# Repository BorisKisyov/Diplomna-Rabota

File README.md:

# Diplomna-Rabota
Дипломната работа на Борис Кисьов. Ученик в ТУЕС от 12"г" клас 2022/2023 година. 
Темата на проекта е "Система за наблюдение на горски масиви на базата на LoRa".

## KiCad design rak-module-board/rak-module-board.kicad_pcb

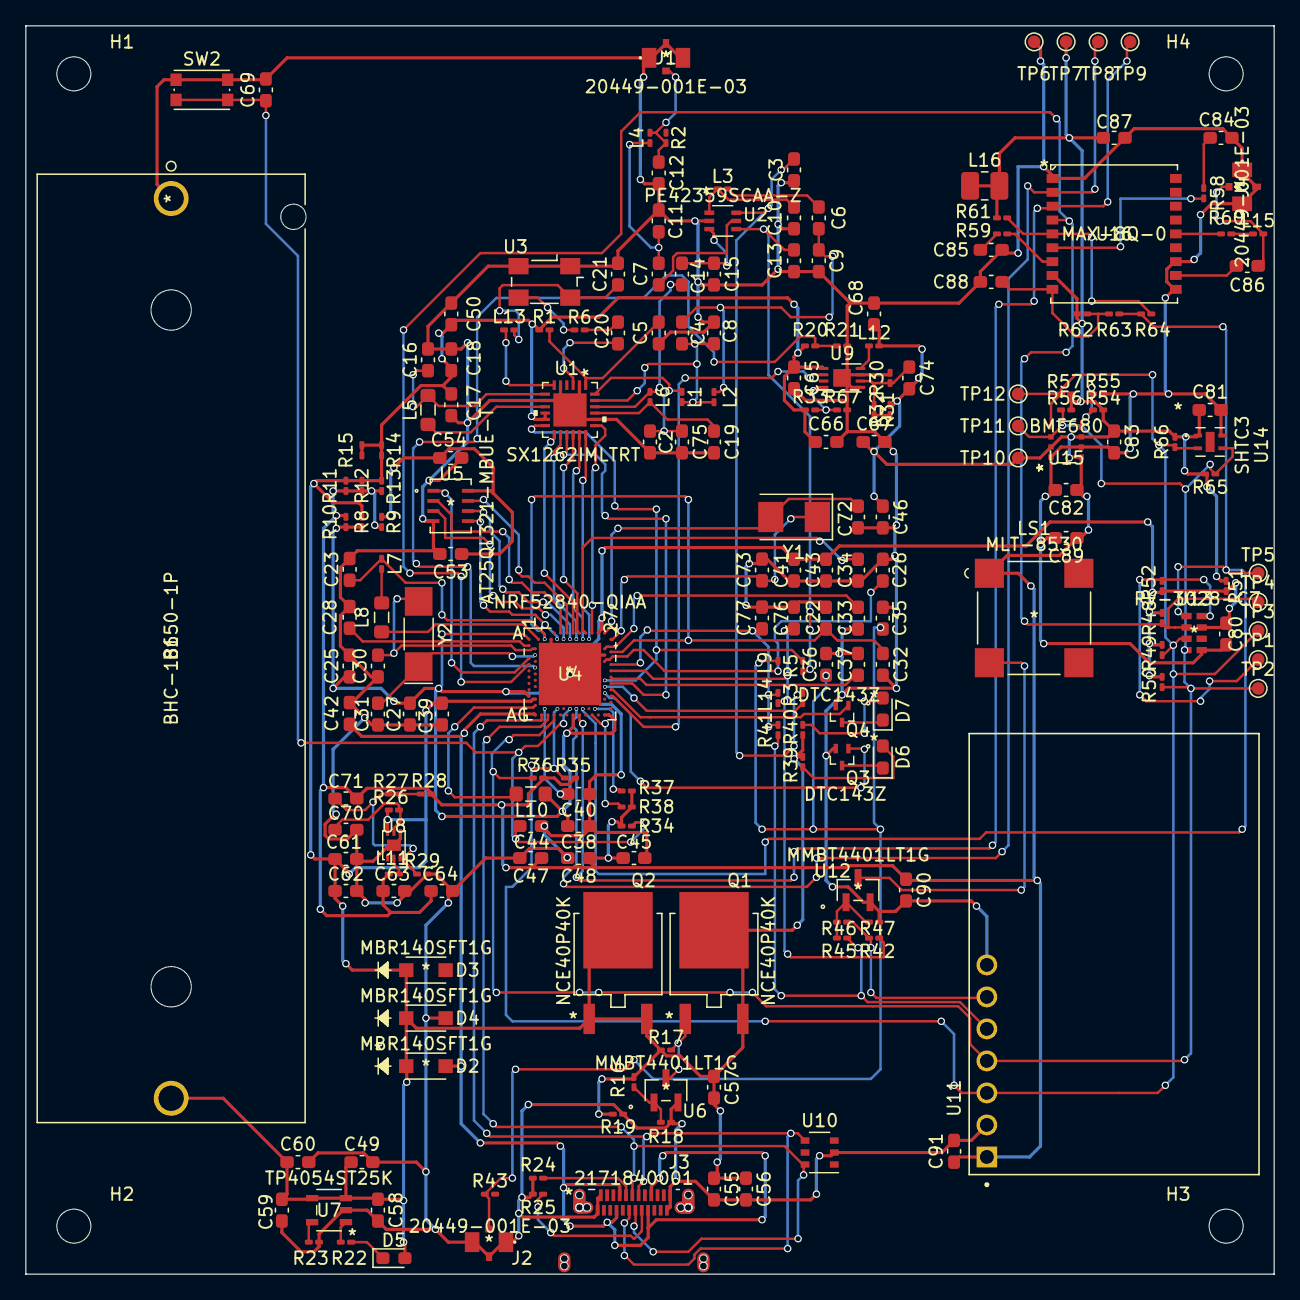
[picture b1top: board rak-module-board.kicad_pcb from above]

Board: 2 copper layers, 99.1 x 99.1 mm, 214 parts (0 on the bottom side), 109 nets.

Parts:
B1: BHC-18650-1P
C2: 47pF; C_0603_1608Metric_Pad1.08x0.95mm_HandSolder
C3, C13, C37: 1nF; C_0603_1608Metric_Pad1.08x0.95mm_HandSolder
C4, C22, C25, C58, C70, C88: 1uF; C_0603_1608Metric_Pad1.08x0.95mm_HandSolder
C5: 3pF; C_0603_1608Metric_Pad1.08x0.95mm_HandSolder
C6, C7: 39pF; C_0603_1608Metric_Pad1.08x0.95mm_HandSolder
C8, C15, C26, C32, C36, C45: NC; C_0603_1608Metric_Pad1.08x0.95mm_HandSolder
C9: 5.6pF; C_0603_1608Metric_Pad1.08x0.95mm_HandSolder
C10: 3.3pF; C_0603_1608Metric_Pad1.08x0.95mm_HandSolder
C11, C12: 3.9pF; C_0603_1608Metric_Pad1.08x0.95mm_HandSolder
C14: 2.4pF; C_0603_1608Metric_Pad1.08x0.95mm_HandSolder
C16: 470nF; C_0603_1608Metric_Pad1.08x0.95mm_HandSolder
C17, C18, C21, C27, C28, C41, C43, C44, C47, C48, C49, C50, C53, C54, C55, C56, C57, C61, C62, C63, C64, C65, C66, C67, C68, C69, C75, C80, C81, C82, C83, C85, C87, C89, C90, C91: 100nF; C_0603_1608Metric_Pad1.08x0.95mm_HandSolder
C19: 1.8pF; C_0603_1608Metric_Pad1.08x0.95mm_HandSolder
C20: 10pF; C_0603_1608Metric_Pad1.08x0.95mm_HandSolder
C23: 47nF; C_0603_1608Metric_Pad1.08x0.95mm_HandSolder
C30, C31, C71, C74: 22pF; C_0603_1608Metric_Pad1.08x0.95mm_HandSolder
C33, C86: 100pF; C_0603_1608Metric_Pad1.08x0.95mm_HandSolder
C34, C35: 1pF; C_0603_1608Metric_Pad1.08x0.95mm_HandSolder
C38, C39, C40, C42: 4.7uF; C_0603_1608Metric_Pad1.08x0.95mm_HandSolder
C46, C84: 10uF; C_0603_1608Metric_Pad1.08x0.95mm_HandSolder
C59, C60: 100uF; C_0603_1608Metric_Pad1.08x0.95mm_HandSolder
C72, C73: 12pF; C_0603_1608Metric_Pad1.08x0.95mm_HandSolder
C76, C77: 300pF; C_0603_1608Metric_Pad1.08x0.95mm_HandSolder
D2, D3, D4: MBR140SFT1G
D5: RED; LED_0603_1608Metric_Pad1.05x0.95mm_HandSolder
D6: GREEN; LED_0603_1608Metric_Pad1.05x0.95mm_HandSolder
D7: BLUE; LED_0603_1608Metric_Pad1.05x0.95mm_HandSolder
H1, H2, H3, H4: MountingHole; MountingHole_2.7mm
J1, J2, J4: 20449-001E-03
J3: 2171840001
L1, L15: 47nH; L_0201_0603Metric_Pad0.64x0.40mm_HandSolder
L2: 2.5nH; L_0201_0603Metric_Pad0.64x0.40mm_HandSolder
L3: 4.7nH; L_0201_0603Metric_Pad0.64x0.40mm_HandSolder
L4: 9.1nH; L_0201_0603Metric_Pad0.64x0.40mm_HandSolder
L5: 15uH; L_0805_2012Metric_Pad1.05x1.20mm_HandSolder
L6: 15nH; L_0201_0603Metric_Pad0.64x0.40mm_HandSolder
L7: 13nH; L_0201_0603Metric_Pad0.64x0.40mm_HandSolder
L8, L10: 10uH; L_0805_2012Metric_Pad1.05x1.20mm_HandSolder
L9: 3.9nH; L_0201_0603Metric_Pad0.64x0.40mm_HandSolder
L11: 4.7uH; L_0201_0603Metric_Pad0.64x0.40mm_HandSolder
L12: 2.2uH; L_0201_0603Metric_Pad0.64x0.40mm_HandSolder
L13: 120uH; L_0201_0603Metric_Pad0.64x0.40mm_HandSolder
L14: NC; L_0201_0603Metric_Pad0.64x0.40mm_HandSolder
L16: 120uH; L_1008_2520Metric_Pad1.43x2.20mm_HandSolder
LS1: MLT-8530
Q1, Q2: NCE40P40K
Q3, Q4: DTC143Z; DTC143ZEBTL
R1, R9, R11, R12, R14, R41, R42, R51, R55, R58, R59, R63: 0; R_0201_0603Metric_Pad0.64x0.40mm_HandSolder
R2, R8, R10, R13, R15, R43, R45, R54, R56, R57, R64, R65, R66, R67: NC; R_0201_0603Metric_Pad0.64x0.40mm_HandSolder
R3, R5: 100R; R_0201_0603Metric_Pad0.64x0.40mm_HandSolder
R6: 220; R_0201_0603Metric_Pad0.64x0.40mm_HandSolder
R16: 47K; R_0201_0603Metric_Pad0.64x0.40mm_HandSolder
R17, R19, R32: 100K; R_0201_0603Metric_Pad0.64x0.40mm_HandSolder
R18, R33, R34, R48, R49, R50, R52: 10K; R_0201_0603Metric_Pad0.64x0.40mm_HandSolder
R20, R29: 1M; R_0201_0603Metric_Pad0.64x0.40mm_HandSolder
R21, R28: 1.5M; R_0201_0603Metric_Pad0.64x0.40mm_HandSolder
R22: 1k; R_0201_0603Metric_Pad0.64x0.40mm_HandSolder
R23: 2.7k; R_0201_0603Metric_Pad0.64x0.40mm_HandSolder
R24, R25: 4.7k; R_0201_0603Metric_Pad0.64x0.40mm_HandSolder
R26: 100k; R_0201_0603Metric_Pad0.64x0.40mm_HandSolder
R27: 800k; R_0201_0603Metric_Pad0.64x0.40mm_HandSolder
R30: 32.4K; R_0201_0603Metric_Pad0.64x0.40mm_HandSolder
R31: 2K; R_0201_0603Metric_Pad0.64x0.40mm_HandSolder
R35, R36, R37, R38, R47, R61, R62: 4.7K; R_0201_0603Metric_Pad0.64x0.40mm_HandSolder
R39, R40: 1K; R_0201_0603Metric_Pad0.64x0.40mm_HandSolder
R46: 330; R_0201_0603Metric_Pad0.64x0.40mm_HandSolder
R60: 10; R_0201_0603Metric_Pad0.64x0.40mm_HandSolder
SW2: SW_DPST_x2; SW_Push_1P1T_NO_CK_KMR2
TP1, TP2, TP3, TP4, TP5, TP6, TP7, TP8, TP9, TP10, TP11, TP12: TestPoint; TestPoint_Pad_D1.0mm
U1: SX1262IMLTRT
U2: PE42359SCAA-Z
U3: 32MHz; Oscillator_SMD_Fox_FT5H_5.0x3.2mm
U4: NRF52840-QIAA; NRF52840-QIAA-R
U5: AT25QL321-MBUE-T
U6, U12: MMBT4401LT1G
U7: TP4054ST25K
U8: SGM6036-ADJ
U9: SGM6019; TDFN-8-1EP_3x2mm_P0.5mm_EP1.4x1.4mm
U10: LRC399-04AT1G; TSOP-6_1.65x3.05mm_P0.95mm
U11: SCD30; MODULE_SCD30
U13: RV-3028-C7; RV-3028-C7 32.768KHZ 1PPM-TA-QA
U14: SHTC3
U15: BME680
U16: MAX-8Q-0
Y1: 32MHz; Crystal_SMD_5032-2Pin_5.0x3.2mm
Y2: 32.768K; Crystal_SMD_MicroCrystal_CC4V-T1A-2Pin_5.0x1.9mm_HandSolder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

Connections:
+3V3: C45.1, C46.1, C47.1, C48.1, C63.1, C64.1, C67.1, C68.1, C71.2, C74.2, C81.1, C82.1, C83.1, C87.1, C89.1, C90.1, C91.1, L11.2, L12.2, L16.1, L16.2, LS1.1, R9.1, R10.1, R11.1, R12.1, R13.1, R28.2, R32.2, R34.1, R35.1, R36.1, R37.1, R38.1, R51.1, R54.1, R56.2, R57.2, R61.1, R62.1, R65.2, R66.2, TP7.1, TP10.1, U11.1 (VDD), U14.1 (VDD), U15.2 (CSB), U15.6 (VDDIO), U15.8 (VDD), U16.8 (VCC)
+BATT: B1.2, C17.1, C18.1, C39.1, C49.1, C50.1, C55.1, C56.1, C57.1, C57.2, C58.1, C59.1, C60.1, C61.1, C62.1, C65.1, C66.1, D2.1 (K), D3.1 (K), D4.1 (K), D5.2 (A), Q1.2, Q1.3, Q2.1, Q2.2, Q2.3, R1.1, R8.2, R11.2, R12.2, R13.2, R14.1, R14.2, R15.1, R15.2, R16.1, R17.2, R19.1, R20.1, R26.1, R33.1, R39.1, R40.1, U1.10 (VBAT), U1.11 (VBAT_IO), U4.Y2 (VDDH), U7.3 (BAT), U7.4 (VCC), U8.6 (VIN), U9.1 (VIN)
/32M_TCXO: C20.2, U1.3 (XTA)
/ADC_VBAT: R20.2, R21.1, U4.K2 (P0-05/AIN3)
/ANT_SW: R3.1, U4.T23 (P1-05)
/BUSY: U1.14 (BUSY), U4.B15 (P1-14)
/DEC4_6: C22.1, C23.1, C32.1, L7.1, U4.B5 (DEC4), U4.E24 (DEC6)
/DIO1: U1.13 (DIO1), U4.A14 (P1-15)
/DIO2: R5.1, U1.12 (DIO2), U4.P23 (P1-07)
/DIO3: L13.1, U1.6 (DIO3)
/I2C_SCL: R35.2, R49.2, R57.1, R66.1, TP3.1, TP12.1, U4.AC9 (P0-14), U11.3 (TX/SCL), U13.3 (SCL), U14.2 (SCL), U15.4 (SCK)
/I2C_SCL_2: R37.2, U4.AC21 (P0-25)
/I2C_SDA: R36.2, R50.2, R56.1, R65.1, TP2.1, TP11.1, U4.AD8 (P0-13), U11.4 (RX/SDA), U13.4 (SDA), U14.3 (SDA), U15.3 (SDI)
/I2C_SDA_2: R38.2, U4.AD20 (P0-24)
/IO5: R42.2, R46.1, U11.6 (PWM)
/IO6: R41.2, R45.1, U11.5 (RDY)
/LED1: Q3.1 (B), U4.V23 (P1-03)
/LED2: Q4.1 (B), U4.U24 (P1-04)
/NFC1: C76.1, L14.2, R42.1, U4.L24 (P0-09/NFC1)
/NFC2: C77.1, L14.1, R41.1, U4.J24 (P0-10/NFC2)
/NRESET: U1.15 (NRESET), U4.R24 (P1-06)
/NRF_RESET: C44.1, C69.1, R34.2, SW2.2 (B), U4.AC13 (P0-18/NRESET)
/PO-04/AIN2: R48.2, TP4.1, U4.J1 (P0-04/AIN2), U13.2 (INT), U16.4 (TIMEPULSE)
/QSPI_CLK: U4.B13 (P0-03/AIN1), U5.6
/QSPI_CS: U4.G1 (P0-26), U5.1
/QSPI_DIO0: U4.B9 (P0-30/AIN6), U5.5
/QSPI_DIO1: U4.A10 (P0-29/AIN5), U5.2
/QSPI_DIO2: U4.B11 (P0-28/AIN4), U5.3
/QSPI_DIO3: U4.A12 (P0-02/AIN0), U5.7
/RESET_GPS: C88.1, R62.2, R63.2, U16.9 (RESET_IN)
/SPI_CLK: U1.18 (SCK), U4.B19 (P1-11)
/SPI_MISO: U1.16 (MISO), U4.A16 (P1-13)
/SPI_MOSI: U1.17 (MOSI), U4.B17 (P1-12)
/SPI_NSS: U1.19 (NSS), U4.A20 (P1-10)
/STANDBY: R61.2, R64.2, U16.5 (EXTINT)
/SW2: U4.W24 (P1-02), U9.2 (EN)
/UART1_DE: R63.1, R64.1, TP5.1, U4.AC17 (P0-21), U13.1 (CLKOUT)
/UART1_RX: TP8.1, U4.AC15 (P0-19), U16.2 (TXD)
/UART1_TX: TP9.1, U4.AD16, U16.3 (RXD)
/USB N: J3.A7 (DN1), J3.B7 (DN2), U4.AD4 (D-), U10.4 (I/O4)
/USB P: J3.A6 (DP1), J3.B6 (DP2), U4.AD6 (D+), U10.6 (I/O3)
GND: B1.1, C2.2, C3.1, C4.2, C8.2, C9.2, C10.2, C11.2, C12.2, C13.2, C15.2, C16.2, C17.2, C18.2, C19.2, C21.2, C22.2, C23.2, C25.2, C26.2, C27.2, C28.1, C30.1, C31.1, C32.2, C33.2, C34.2, C35.2, C36.2, C37.2, C38.2, C39.2, C40.2, C41.2, C42.2, C43.2, C44.2, C45.2, C46.2, C47.2, C48.2, C49.2, C50.2, C53.2, C54.2, C55.2, C56.2, C58.2, C59.2, C60.2, C61.2, C62.2, C63.2, C64.2, C65.2, C66.2, C67.2, C68.2, C69.2, C70.2, C72.2, C73.2, C75.2, C76.2, C77.2, C80.2, C81.2, C82.2, C83.2, C84.2, C85.2, C87.2, C88.2, C89.2, C90.2, C91.2, D4.2 (A), J1.1, J1.2, J1.3, J2.1, J2.2, J2.3, J3.A1 (GND), J3.A12 (GND), J3.B1 (GND), J3.B12 (GND), J4.1, J4.2, J4.3, Q3.2 (E), Q4.2 (E), R18.2, R19.2, R21.2, R23.2, R24.1, R25.2, R29.2, R30.2, R47.2, R55.2, R67.2, SW2.1 (A), TP6.1, U1.2 (GND), U1.5 (GND), U1.8 (GND), U1.20 (GND), U1.25 (GND), U2.2 (GND), U3.1 (VC), U3.2 (GND), U4.74 (VSS), U4.B7 (VSS), U4.F23 (VSS_PA), U5.4, U6.2 (EMITTER), U7.2 (GND), U8.4 (GND), U8.7 (EXPAD), U9.5 (SGND), U9.7 (PGND), U9.9 (EXPAD), U10.2 (GND), U11.2 (GND), U11.7 (SEL), U12.2 (EMITTER), U13.5 (VSS), U14.4 (VSS), U15.1 (GND), U15.7 (GND), U16.1 (GND), U16.10 (GND), U16.12 (GND)
unnamed: C2.1, C75.1, L1.1, U1.24 (VR_PA)
unnamed: C3.2, R3.2, U2.6 (*CTRL/VDD)
unnamed: C4.1, R1.2, U1.1 (VDD_IN)
unnamed: C5.1, C8.1, L1.2, L2.1, U1.23 (RFO)
unnamed: C5.2, C6.1, C9.1, L2.2
unnamed: C6.2, L3.1
unnamed: C7.1, U2.5 (RFC)
unnamed: C10.1, L3.2, U2.1 (RF1)
unnamed: C7.2, C11.1, L4.1
unnamed: C12.1, J1.4, L4.2, R2.1
unnamed: C13.1, R5.2, U2.4 (CTRL)
unnamed: C14.1, L6.2, U1.22 (RFI_N)
unnamed: C14.2, C15.1, U2.3 (RF2)
unnamed: C16.1, L5.1, U1.7 (VREG)
unnamed: C19.1, L6.1, U1.21 (RFI_P)
unnamed: C20.1, R6.2
unnamed: C21.1, L13.2, U3.4 (VDD)
unnamed: C26.1, U4.A18 (DEC2)
unnamed: C28.2, U4.C1 (DEC1)
unnamed: C30.2, U4.D2 (P0-00/XL1), Y2.2
unnamed: C31.2, U4.F2 (P0-01/XL2), Y2.1
unnamed: C33.1, U4.D23 (DEC3)
unnamed: C34.1, L9.1, U4.H23 (ANT)
unnamed: C35.1, C36.1, J2.4, L9.2, R43.1
unnamed: C37.1, U4.N24 (DEC5)
unnamed: C40.1, U4.AC5 (DECUSB)
unnamed: C70.1, R26.2, U8.5 (EN)
unnamed: C71.1, R27.1, R29.1, U8.3 (OUT)
unnamed: C72.1, U4.A23 (XC2), Y1.2
unnamed: C73.1, U4.B24 (XC1), Y1.1
unnamed: C74.1, R30.1, R31.1, U9.6 (FB)
unnamed: C84.1, R58.1
unnamed: C85.1, R59.1
unnamed: C86.1, U16.11 (RF_IN)
unnamed: C86.2, J4.4, L15.2
unnamed: D5.1 (K), R22.1
unnamed: D6.1 (K), Q3.3 (C)
unnamed: D6.2 (A), R39.2
unnamed: D7.1 (K), Q4.3 (C)
unnamed: D7.2 (A), R40.2
unnamed: J3.A5 (CC1), R24.2
unnamed: J3.B5 (CC2), R25.1
unnamed: L5.2, U1.9 (DCC_SW)
unnamed: L7.2, L8.1
unnamed: L8.2, U4.B3 (DCC)
unnamed: L10.2, U4.AB2 (DCCH)
unnamed: L11.1, U8.2 (SW)
unnamed: L12.1, U9.8 (SW)
unnamed: L15.1, R60.2
unnamed: LS1.2, U12.3 (COLLECTOR)
unnamed: Q1.1, R17.1, U6.3 (COLLECTOR)
unnamed: R6.1, U3.3 (OUT)
unnamed: R16.2, R18.1, U6.1 (BASE)
unnamed: R22.2, U7.1 (*CHRG)
unnamed: R23.1, U7.5 (PROG)
unnamed: R27.2, R28.1
unnamed: R31.2, R32.1
unnamed: R33.2, R67.1, U9.4 (MODE)
unnamed: R45.2, R46.2, R47.1, U12.1 (BASE)
unnamed: R52.2, TP1.1, U13.8 (EVI)
unnamed: R54.2, R55.1, U15.5 (SDO)
unnamed: R58.2, U16.6 (V_BCKP)
unnamed: R59.2, U16.7 (VCC_IO)
unnamed: R60.1, U16.14 (VCC_RF)
VBUS: C42.1, D2.2 (A), J3.A4 (VBUS), J3.A9 (VBUS), J3.B4 (VBUS), J3.B9 (VBUS), U4.AD2 (VBUS)
VD: C53.1, C54.1, R9.2, U5.8
VDD: C25.1, C27.1, C38.1, C41.1, C43.1, C80.1, L10.1, R8.1, R10.2, R48.1, R49.1, R50.1, R51.2, R52.1, U4.A22 (VDD), U4.AD14 (VDD), U4.AD23 (VDD), U4.B1 (VDD), U4.W1 (VDD), U13.7 (VDD)

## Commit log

2023-02-01 Add files via upload
    Документация по Дипломната работа

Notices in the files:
parts and their libraries:
Copyright 2021 Accelerated Designs. All rights reserved.
